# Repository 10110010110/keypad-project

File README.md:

# keypad-project
 Personal Project for CCI

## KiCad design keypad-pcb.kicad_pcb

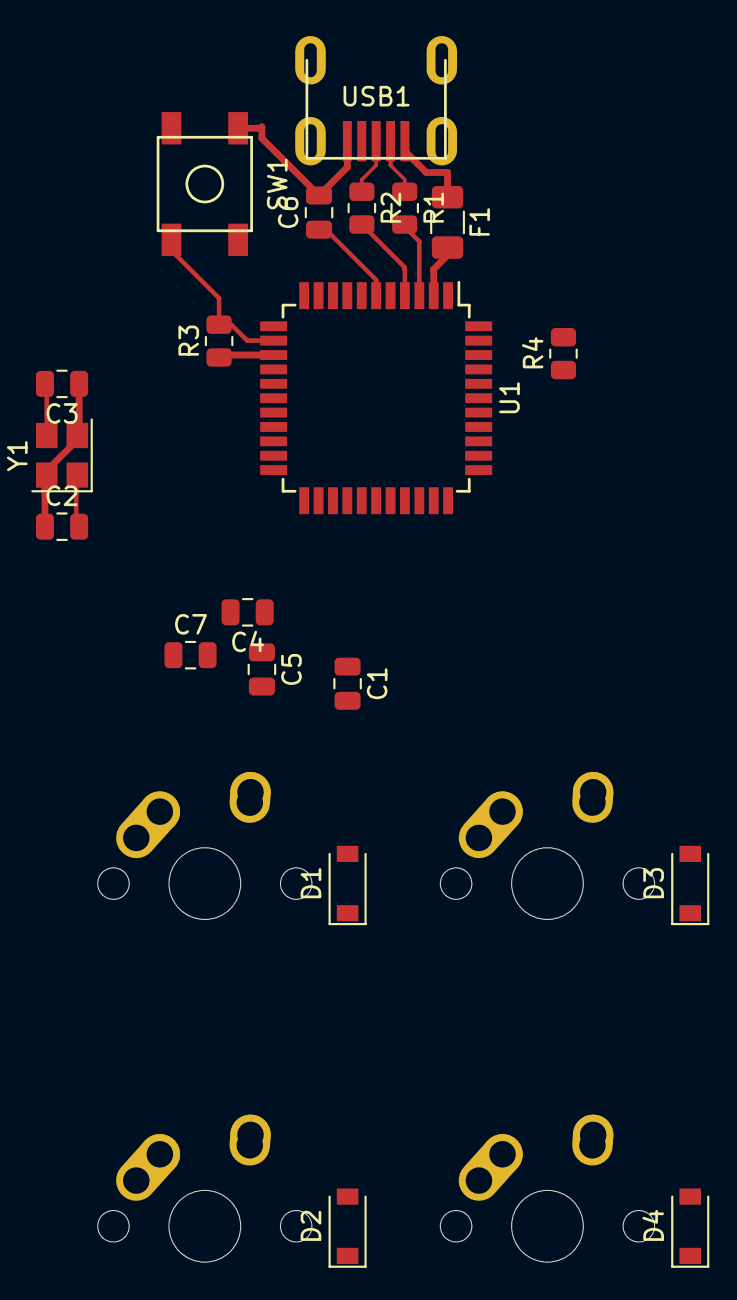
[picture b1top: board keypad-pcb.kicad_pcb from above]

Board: 2 copper layers, 24 parts (0 on the bottom side), 20 nets.

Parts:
C1, C4, C5: 0.1uF; C_0805_2012Metric
C2, C3: 22pF; C_0805_2012Metric
C6: 1uF; C_0805_2012Metric
C7: 10uF; C_0805_2012Metric
D1, D2, D3, D4: D_Small; D_SOD-123
F1: 500mA; Fuse_1206_3216Metric
MX1, MX2, MX3, MX4: MX-NoLED; MX-1U-NoLED
R1, R2: 22; R_0805_2012Metric
R3, R4: 10k; R_0805_2012Metric
SW1: SW_Push; SKQG-1155865
U1: ATmega32U4-A; TQFP-44_10x10mm_P0.8mm
USB1: Molex-0548190589
Y1: 16MHz; Crystal_SMD_3225-4Pin_3.2x2.5mm

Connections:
+5V: C1.1, C4.1, C5.1, C7.1, F1.2, R3.1, U1.2 (UVCC), U1.7 (VBUS), U1.14 (VCC), U1.24 (AVCC), U1.34 (VCC), U1.44 (AVCC)
COL0: MX1.1 (COL), MX2.1 (COL)
COL1: MX3.1 (COL), MX4.1 (COL)
D+: R2.1, USB1.3 (D+)
D-: R1.1, USB1.4 (D-)
GND: C1.2, C2.1, C3.1, C4.2, C5.2, C6.2, C7.2, R4.2, SW1.1, U1.5 (UGND), U1.15 (GND), U1.23 (GND), U1.35 (GND), U1.43 (GND), USB1.1 (GND), Y1.2, Y1.4
unnamed: C2.2, U1.17 (XTAL1), Y1.1
unnamed: C3.2, U1.16 (XTAL2), Y1.3
unnamed: C6.1, U1.6 (UCAP)
unnamed: D1.2 (A), MX1.2 (ROW)
unnamed: D2.2 (A), MX2.2 (ROW)
unnamed: D3.2 (A), MX3.2 (ROW)
unnamed: D4.2 (A), MX4.2 (ROW)
unnamed: R1.2, U1.3 (D-)
unnamed: R2.2, U1.4 (D+)
unnamed: R3.2, SW1.2, U1.13 (~RESET)
unnamed: R4.1, U1.33 (~HWB/PE2)
ROW0: D1.1 (K), D3.1 (K)
ROW1: D2.1 (K), D4.1 (K)
VCC: F1.1, USB1.5 (VBUS)

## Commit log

2022-11-02 Initialization of PCB
2022-11-02 Add submodules
2022-11-02 Added footprint libs
2022-11-02 Setup MCU
2022-11-16 Added USB, switch grid and footprints
2022-11-16 Started Layout for PCB
2022-11-24 More Wiring
2022-12-02 Finished schematic (no LEDs), Started routing PCB
